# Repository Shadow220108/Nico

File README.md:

<h1 align="center">
  <br>

  <br>
  Nico
  <br>
</h1>
<h3 align="center">
Ultra-compact USB dongle with a 56-LED Charlieplexed visualizer and native CH552 8051 control.
</h3>

| Spinnyy |
| --- |
|  |

| Front Render | Back Render | 
| --- | --- |
|| | 

## PCB Design 
| |
|--- |  

 ### The PCB is 2 layers with dimensions 76 by 21 mm

## Schematics  

Here are the schematic designs,

| |
| --- |  

## How can you get one for yourself? 

That is pretty easy, you have all the files you will need in the production folder, order the development  
board from any PCB fab ( I chose JLC cause its cheap and has good quality ) and BINGO! You will have it  
to use for any purpose you want!  

## BOM  
|Name|Purpose          |Quantity|Total Cost (USD)|Link               |Distributor|
|----|-----------------|--------|----------------|-------------------|-----------|
|PCB |Development Board|5       |43.09 ( After coupons )           |https://jlcpcb.com/|JLCPCB     |
|Components |all the components grouped together|1       |      28.75    |https://www.lcsc.com|LCSC     |
| | | Total | 71.84 | 

LCSC BOM for the components on board is [here](https://github.com/Shadow220108/Nico/blob/main/production/bom.csv)

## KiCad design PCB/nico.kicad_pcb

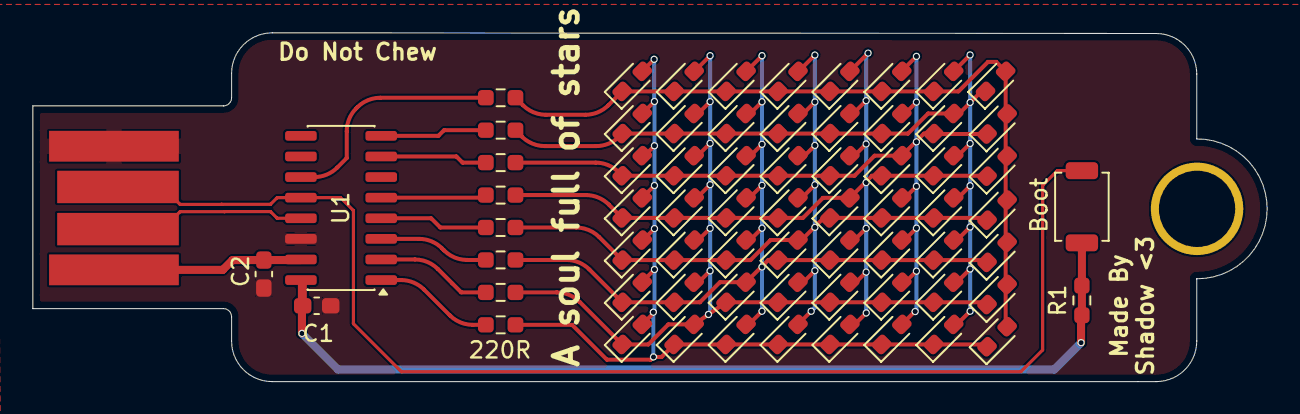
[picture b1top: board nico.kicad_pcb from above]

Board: 2 copper layers, 76.1 x 21.5 mm, 70 parts (0 on the bottom side), 14 nets.

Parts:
220R: 220R; R_0603_1608Metric_Pad0.98x0.95mm_HandSolder
Boot: Boot; SW_SPST_TS-1088-xR020
C1, C2: 100nF; C_0603_1608Metric_Pad1.08x0.95mm_HandSolder
D1, D2, D3, D4, D5, D6, D7, D8, D9, D10, D11, D12, D13, D14, D15, D16, D17, D18, D19, D20, D21, D22, D23, D24, D25, D26, D27, D28, D29, D30, D31, D32, D33, D34, D35, D36, D37, D38, D39, D40, D41, D42, D43, D44, D45, D46, D47, D48, D49, D50, D51, D52, D53, D54, D55, D56: RED; LED_0603_1608Metric_Pad1.05x0.95mm_HandSolder
J1: USB_A; USB-A
R1: 10k; R_0603_1608Metric_Pad0.98x0.95mm_HandSolder
R3, R4, R5, R6, R7, R8, R9: 220R; R_0603_1608Metric_Pad0.98x0.95mm_HandSolder
U1: CH552G; SOIC-16_3.9x9.9mm_P1.27mm

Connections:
+3V3: C1.1, R1.1, U1.16 (V33)
/D+: Boot.1, J1.3 (D+), U1.12 (P3.6/UDP)
/D-: J1.2 (D-), U1.13 (P3.7/UDM)
/ROW0: 220R.1, 220R.2, D1.1 (K), D8.1 (K), D15.1 (K), D22.1 (K), D29.1 (K), D36.1 (K), D43.1 (K), D50.2 (A), D51.2 (A), D52.2 (A), D53.2 (A), D54.2 (A), D55.2 (A), D56.2 (A), U1.11 (P3.4/PWM2/RXD1_/T0)
/ROW1: D2.1 (K), D9.1 (K), D16.1 (K), D23.1 (K), D30.1 (K), D37.1 (K), D43.2 (A), D44.2 (A), D45.2 (A), D46.2 (A), D47.2 (A), D48.2 (A), D49.2 (A), D50.1 (K), R3.1, R3.2, U1.8 (P3.0/PWM1_/RXD)
/ROW2: D3.1 (K), D10.1 (K), D17.1 (K), D24.1 (K), D31.1 (K), D36.2 (A), D37.2 (A), D38.2 (A), D39.2 (A), D40.2 (A), D41.2 (A), D42.2 (A), D44.1 (K), D51.1 (K), R4.1, R4.2, U1.7 (P3.1/PWM2_/TXD)
/ROW3: D4.1 (K), D11.1 (K), D18.1 (K), D25.1 (K), D29.2 (A), D30.2 (A), D31.2 (A), D32.2 (A), D33.2 (A), D34.2 (A), D35.2 (A), D38.1 (K), D45.1 (K), D52.1 (K), R5.1, R5.2, U1.5 (P1.7/SCK/TXD1/TIN5)
/ROW4: D5.1 (K), D12.1 (K), D19.1 (K), D22.2 (A), D23.2 (A), D24.2 (A), D25.2 (A), D26.2 (A), D27.2 (A), D28.2 (A), D32.1 (K), D39.1 (K), D46.1 (K), D53.1 (K), R6.1, R6.2, U1.4 (P1.6/MISO/RXD1/TIN4)
/ROW5: D6.1 (K), D13.1 (K), D15.2 (A), D16.2 (A), D17.2 (A), D18.2 (A), D19.2 (A), D20.2 (A), D21.2 (A), D26.1 (K), D33.1 (K), D40.1 (K), D47.1 (K), D54.1 (K), R7.1, R7.2, U1.3 (P1.5/MOSI/PWM1/TIN3/UCC2/AIN2)
/ROW6: D7.1 (K), D8.2 (A), D9.2 (A), D10.2 (A), D11.2 (A), D12.2 (A), D13.2 (A), D14.2 (A), D20.1 (K), D27.1 (K), D34.1 (K), D41.1 (K), D48.1 (K), D55.1 (K), R8.1, R8.2, U1.2 (P1.4/T2_/CAP1_/SCS/TIN2/UCC1/AIN1)
/ROW7: D1.2 (A), D2.2 (A), D3.2 (A), D4.2 (A), D5.2 (A), D6.2 (A), D7.2 (A), D14.1 (K), D21.1 (K), D28.1 (K), D35.1 (K), D42.1 (K), D49.1 (K), D56.1 (K), R9.1, R9.2, U1.1 (P3.2/TXD1_/INT0/VBUS1/AIN3)
GND: C1.2, C2.2, J1.4 (GND), U1.14 (GND/VSS)
unnamed: Boot.2, R1.2
VBUS: C2.1, J1.1 (VBUS), U1.15 (VCC/VDD)

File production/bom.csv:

Designator,Footprint,Quantity,Value,LCSC Part #
"220R, R3, R4, R5, R6, R7, R8, R9",0603,8,220R,
BOOT,SW_SPST_TS-1088-xR020,1,Boot,
"C1, C2",0603,2,100nF,
"D1, D10, D11, D12, D13, D14, D15, D16, D17, D18, D19, D2, D20, D21, D22, D23, D24, D25, D26, D27, D28, D29, D3, D30, D31, D32, D33, D34, D35, D36, D37, D38, D39, D4, D40, D41, D42, D43, D44, D45, D46, D47, D48, D49, D5, D50, D51, D52, D53, D54, D55, D56, D6, D7, D8, D9",0603,56,RED,
J1,USB-A,1,USB_A,
R1,0603,1,10k,
U1,SOIC-16_3.9x9.9mm_P1.27mm,1,CH552G,C111292
